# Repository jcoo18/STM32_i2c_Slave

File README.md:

This Repo contains the firmware and hardware breakout pcb files for the timmer capture device for I2C logging to the Openlog

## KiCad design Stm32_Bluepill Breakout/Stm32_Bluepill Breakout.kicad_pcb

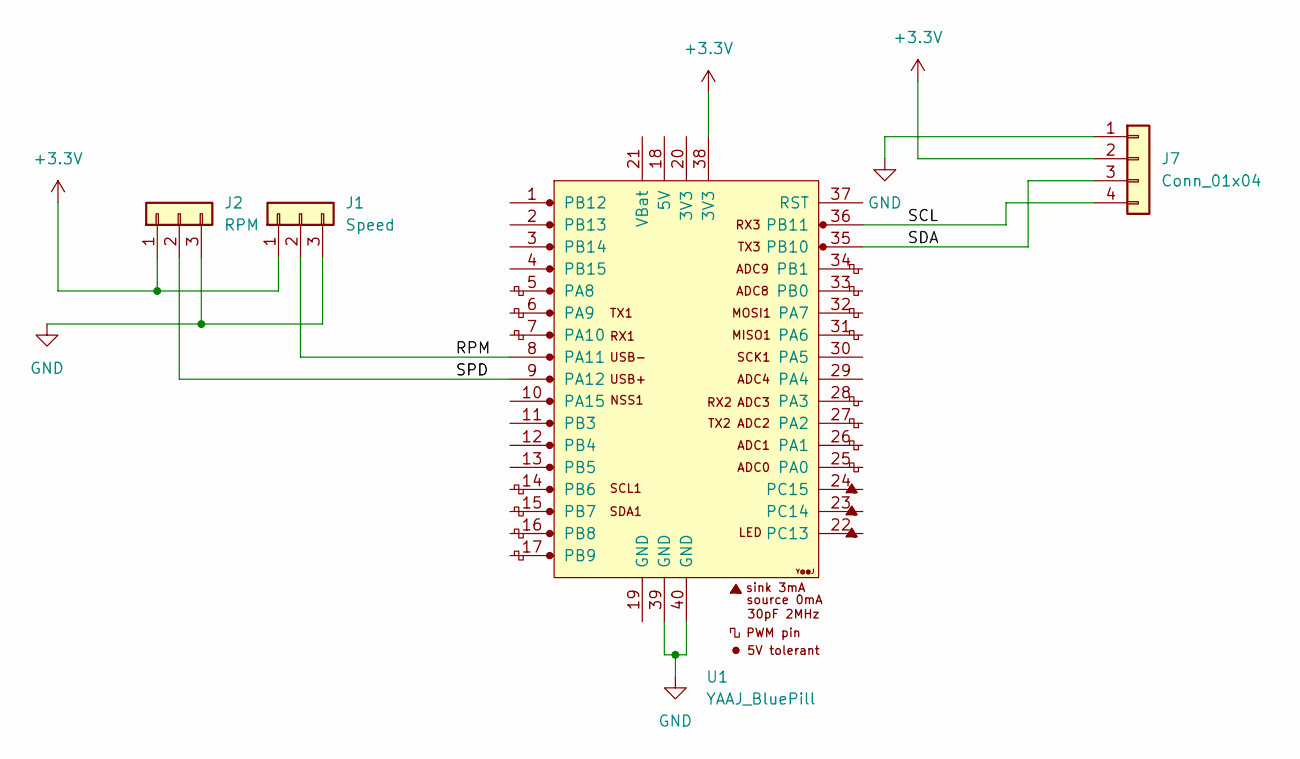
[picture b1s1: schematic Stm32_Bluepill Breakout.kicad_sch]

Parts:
J1: Speed; Molex_KK-254_AE-6410-03A_1x03_P2.54mm_Vertical
J2: RPM; Molex_KK-254_AE-6410-03A_1x03_P2.54mm_Vertical
J7: Conn_01x04; Molex_KK-254_AE-6410-04A_1x04_P2.54mm_Vertical
U1: YAAJ_BluePill; YAAJ_BluePill_1

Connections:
+3.3V: J1.1, J2.1, J7.2, U1.38 (3V3)
/RPM: J1.2, U1.8 (PA11)
/SCL: J7.4, U1.36 (PB11)
/SDA: J7.3, U1.35 (PB10)
/SPD: J2.2, U1.9 (PA12)
GND: J1.3, J2.3, J7.1, U1.39 (GND), U1.40 (GND)

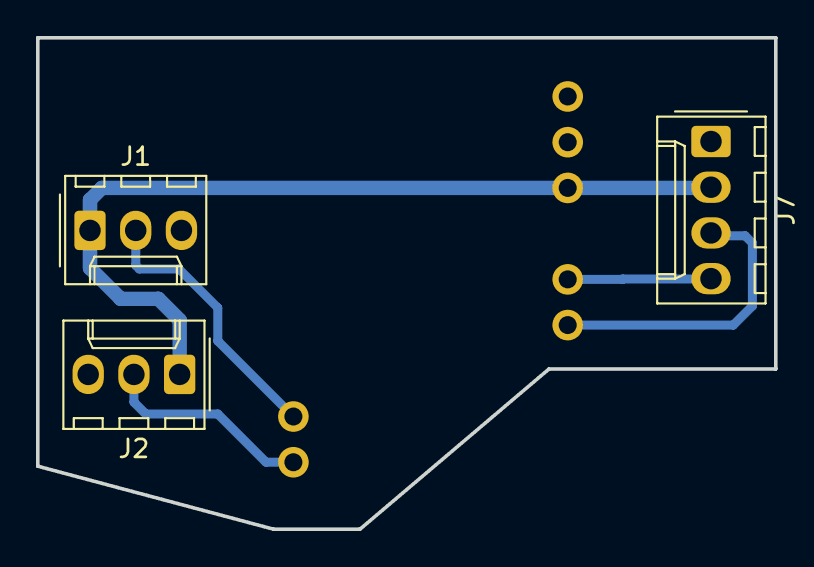
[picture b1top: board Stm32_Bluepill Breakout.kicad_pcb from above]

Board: 2 copper layers, 41.0 x 27.3 mm, 4 parts (0 on the bottom side), 6 nets.

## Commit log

2024-07-03 Upload
2024-07-12 Updated pin defines
2024-07-27 Tested
2024-07-27 removed unnecessary lib files
2024-07-27 re organised files
2024-08-18 Renamed tested build to v1.0
2024-08-18 Active file v1.0
2024-08-18 Added breakout hardware docs
2024-08-19 reduced interrupts to only two physical counters and I2C
2024-08-19 Reduced interrupts to two physical counters and I2C
2024-08-25 Changed to reflect calcs by InterlinkKnight
2024-08-25 updated naming
2024-09-06 Changed AmountOfReadings to 6
